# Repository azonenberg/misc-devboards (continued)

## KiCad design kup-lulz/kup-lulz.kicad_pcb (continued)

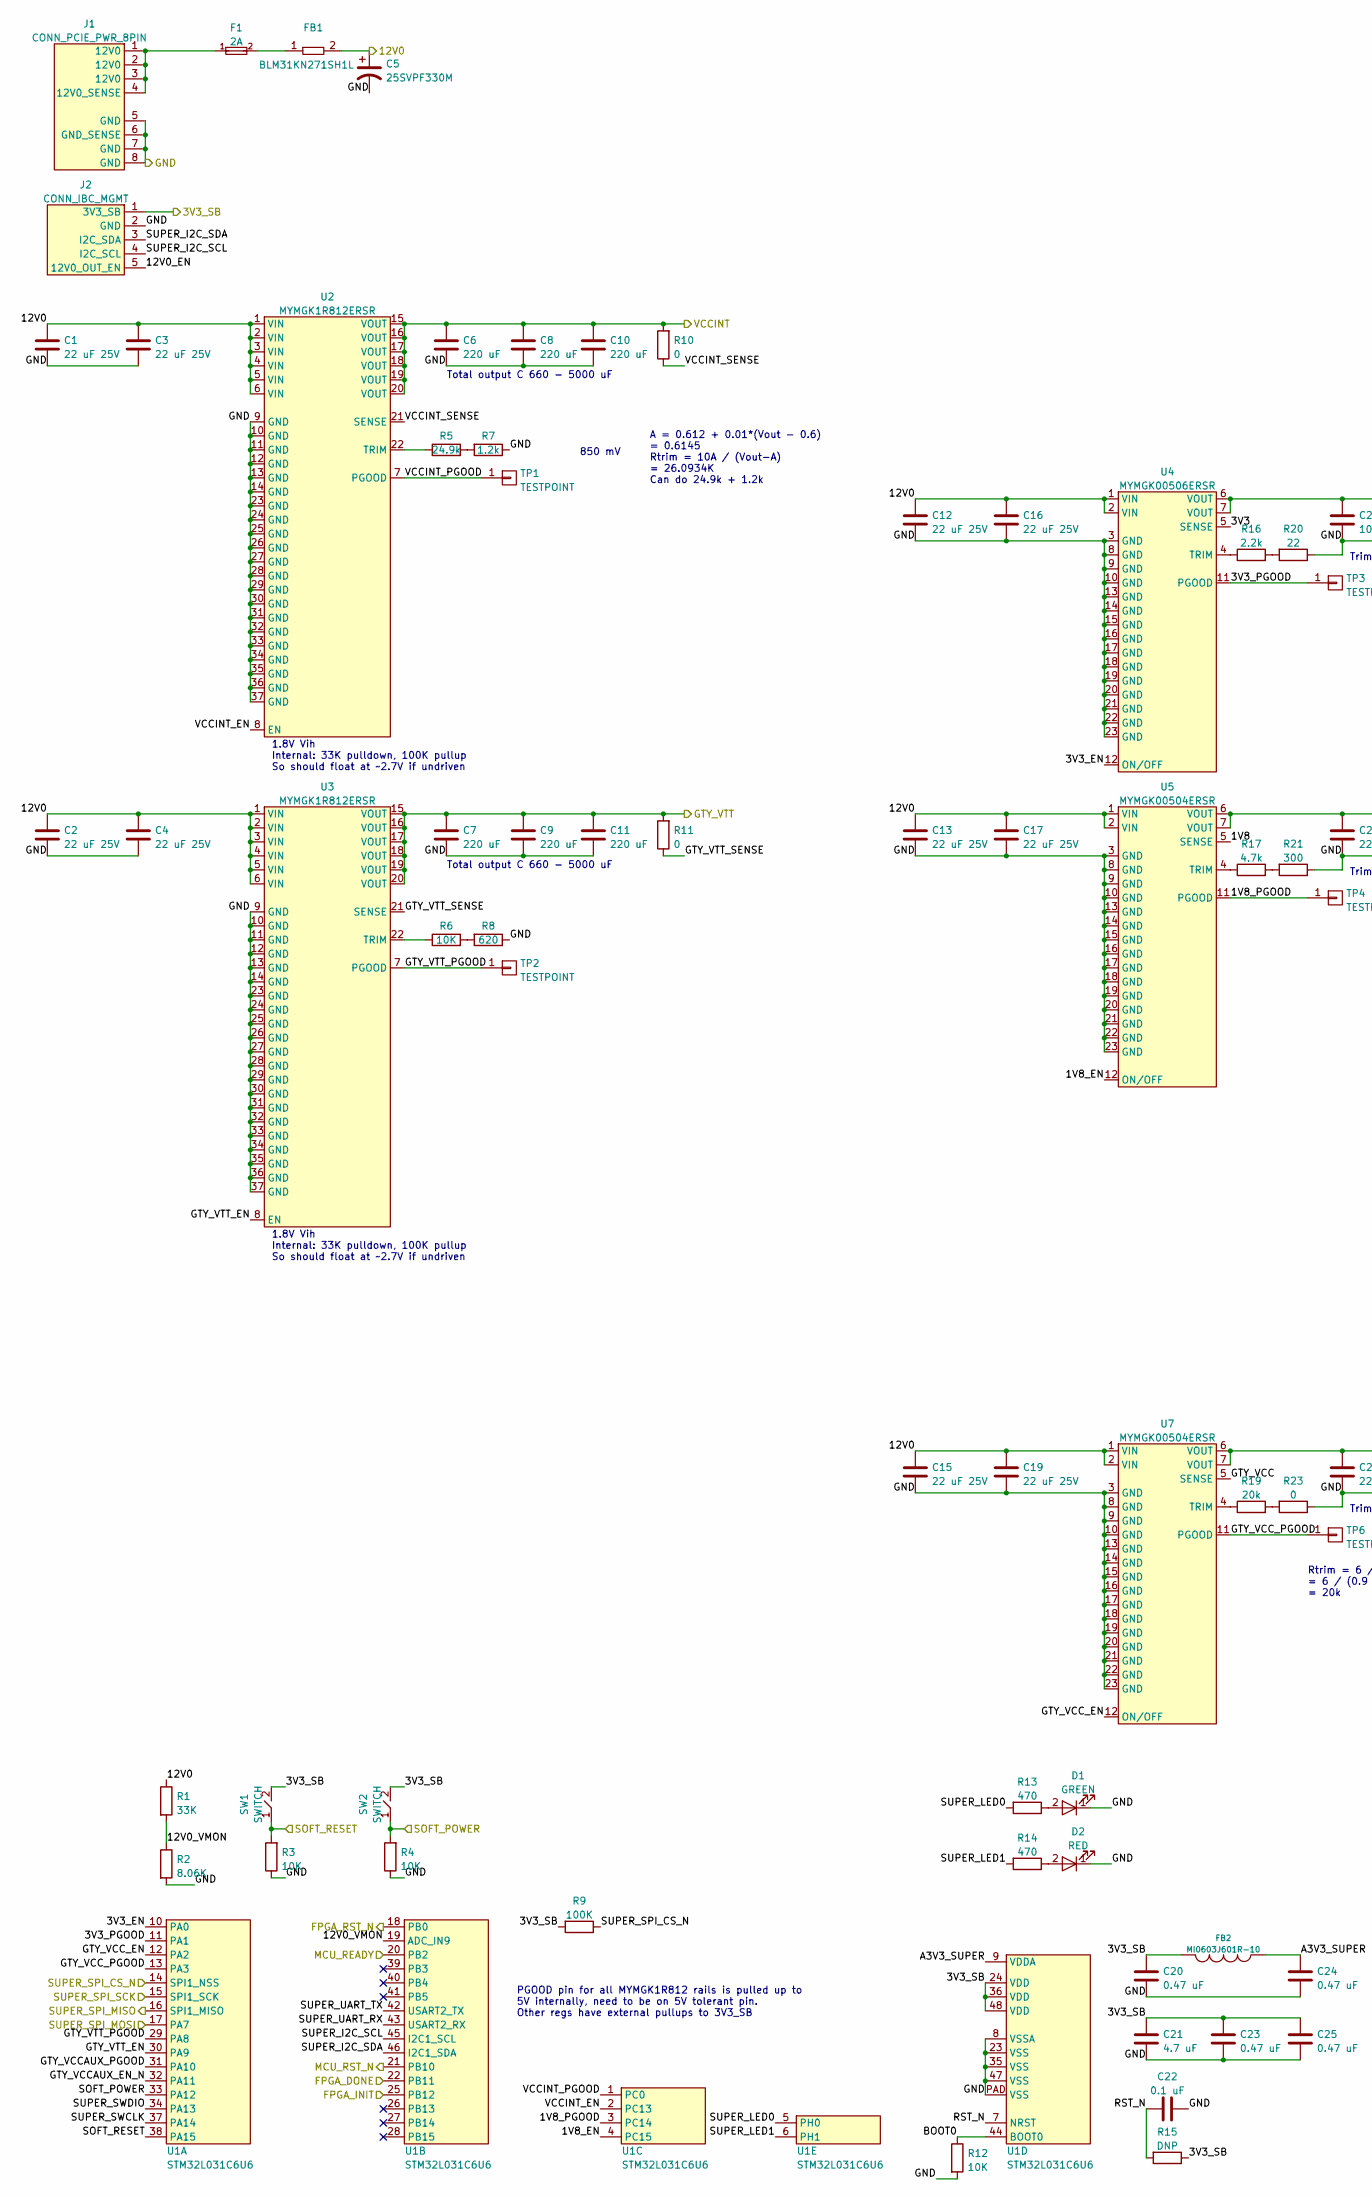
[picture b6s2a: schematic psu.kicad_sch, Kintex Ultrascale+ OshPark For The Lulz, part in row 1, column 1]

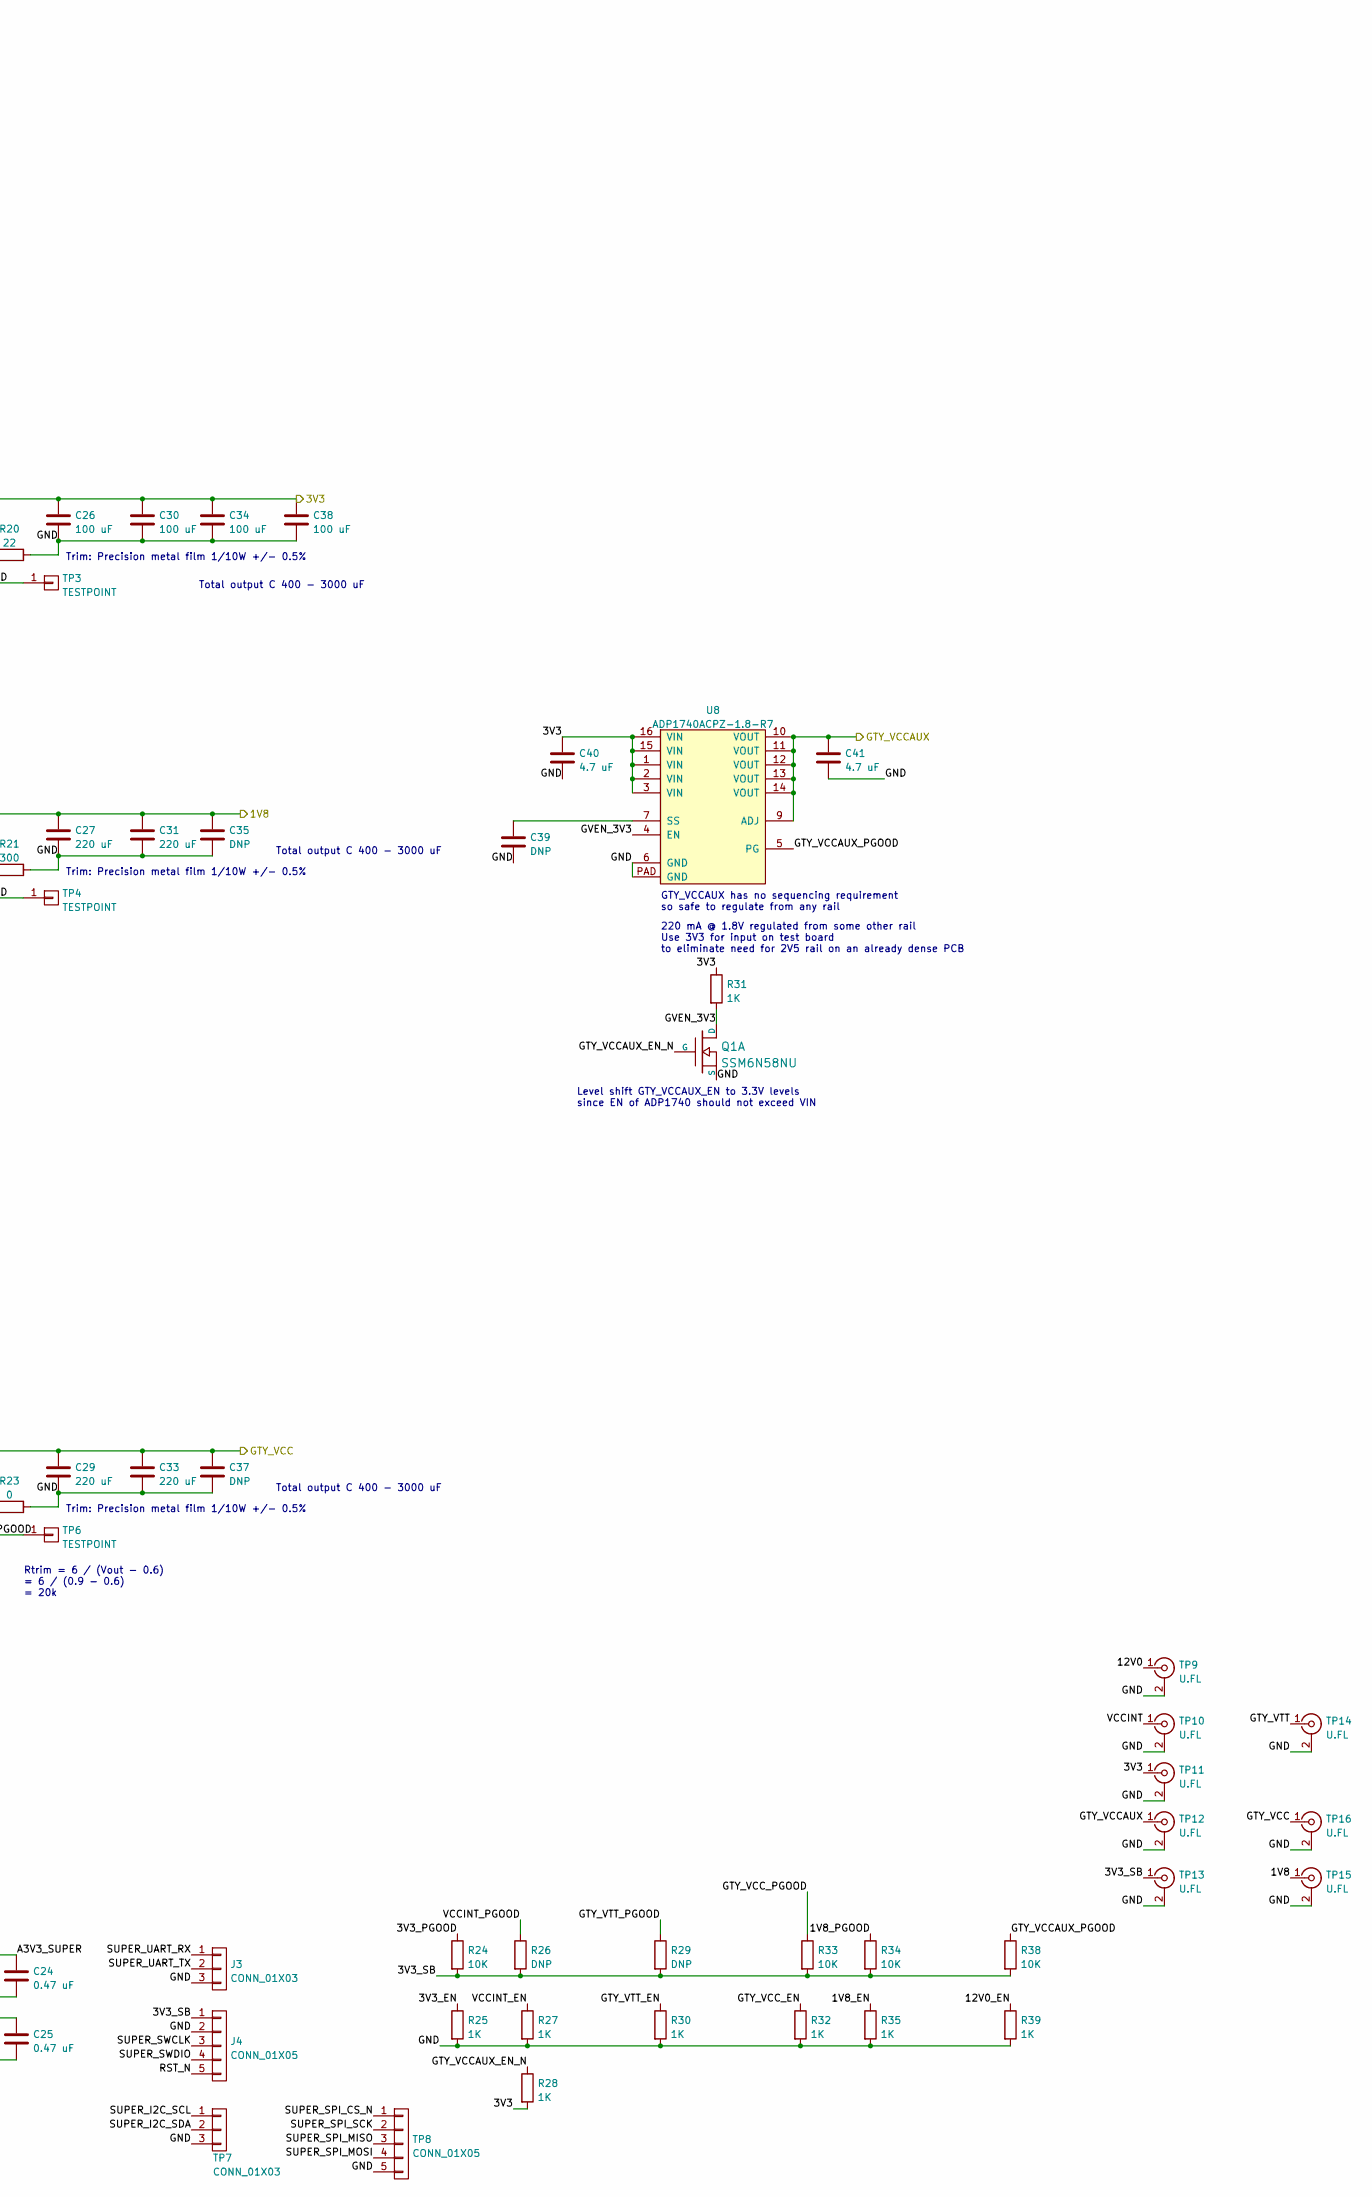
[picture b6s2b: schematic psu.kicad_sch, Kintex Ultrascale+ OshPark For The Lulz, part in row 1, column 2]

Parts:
C1, C2, C3, C4, C12, C13, C15, C16, C17, C19: 22 uF 25V; EIA_1812_CAP_NOSILK
C5: 25SVPF330M; CAP_AL_10MM_SMT
C6, C7, C8, C9, C10, C11, C27, C29, C31, C33: 220 uF; EIA_1210_CAP_NOSILK
C20, C23, C24, C25: 0.47 uF; EIA_0402_CAP_NOSILK
C21, C40, C41: 4.7 uF; EIA_0603_CAP_NOSILK
C22: 0.1 uF; EIA_0402_CAP_NOSILK
C26, C30, C34, C38: 100 uF; EIA_1210_CAP_NOSILK
C35, C37: DNP; EIA_1210_CAP_NOSILK
C39: DNP; EIA_0402_CAP_NOSILK
D1: GREEN; EIA_0603_LED
D2: RED; EIA_0603_LED
F1: 2A; EIA_0603_CAP_NOSILK
FB1: BLM31KN271SH1L; EIA_1206_CAP_NOSILK
FB2: MI0603J601R-10; EIA_0603_INDUCTOR_NOSILK
J1: CONN_PCIE_PWR_8PIN; CONN_MOLEX_MINIFITJR_8POS_0039291087
J2: CONN_IBC_MGMT; CONN_MOLEX_PICOBLADE_5POS_0532610571
J3: CONN_01X03; CONN_HEADER_2.54MM_1x3
J4: CONN_01X05; CONN_HEADER_2.54MM_1x5
Q1: SSM6N58NU; DFN_6_0.65MM_2x2MM_GDS
R1: 33K; EIA_0402_RES_NOSILK
R2: 8.06K; EIA_0402_RES_NOSILK
R3, R4, R6, R12, R24, R33, R34, R38: 10K; EIA_0402_RES_NOSILK
R5: 24.9k; EIA_0402_RES_NOSILK
R7: 1.2k; EIA_0402_RES_NOSILK
R8: 620; EIA_0402_RES_NOSILK
R9: 100K; EIA_0402_RES_NOSILK
R10, R11, R23: 0; EIA_0402_RES_NOSILK
R13, R14: 470; EIA_0402_RES_NOSILK
R15, R26, R29: DNP; EIA_0402_RES_NOSILK
R16: 2.2k; EIA_0402_RES_NOSILK
R17: 4.7k; EIA_0402_RES_NOSILK
R19: 20k; EIA_0402_RES_NOSILK
R20: 22; EIA_0402_RES_NOSILK
R21: 300; EIA_0402_RES_NOSILK
R25, R27, R28, R30, R31, R32, R35, R39: 1K; EIA_0402_RES_NOSILK
SW1, SW2: SWITCH; SWITCH_RAFI_MICON_5
TP1, TP2, TP3, TP4, TP6: TESTPOINT; TESTPOINT_SMT_0.5MM
TP7: CONN_01X03; CONN_HEADER_2.54MM_1x3
TP8: CONN_01X05; CONN_HEADER_2.54MM_1x5
TP9, TP10, TP11, TP12, TP13, TP14, TP15, TP16: U.FL; CONN_U.FL_TE_1909763-1
U1: STM32L031C6U6; QFN_48_0.5MM_7x7MM
U2, U3: MYMGK1R812ERSR; MODULE_MURATA_MYMGK1R812
U4: MYMGK00506ERSR; MODULE_MURATA_MYMGK00504ERSR
U5, U7: MYMGK00504ERSR; MODULE_MURATA_MYMGK00504ERSR
U8: ADP1740ACPZ-1.8-R7; QFN_16_0.65MM_4x4MM

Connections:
/3V3: C26.1, C30.1, C34.1, C38.1, C40.1, R28.2, R31.1, TP11.1 (In), U4.5 (SENSE), U4.6 (VOUT), U4.7 (VOUT), U8.1 (VIN), U8.2 (VIN), U8.3 (VIN), U8.15 (VIN), U8.16 (VIN); also elsewhere on the board
/3V3_SB: C20.1, C21.1, C23.1, C25.1, FB2.2, J2.1 (3V3_SB), J4.1, R9.2, R15.1, R24.2, R26.2, R29.2, R33.2, R34.2, R38.2, SW1.2, SW2.2, TP13.1 (In), U1.24 (VDD), U1.36 (VDD), U1.48 (VDD)
/12V0: C1.1, C2.1, C3.1, C4.1, C5.1, C12.1, C13.1, C15.1, C16.1, C17.1, C19.1, FB1.2, R1.1, TP9.1 (In), U2.1 (VIN), U2.2 (VIN), U2.3 (VIN), U2.4 (VIN), U2.5 (VIN), U2.6 (VIN), U3.1 (VIN), U3.2 (VIN), U3.3 (VIN), U3.4 (VIN), U3.5 (VIN), U3.6 (VIN), U4.1 (VIN), U4.2 (VIN), U5.1 (VIN), U5.2 (VIN), U7.1 (VIN), U7.2 (VIN)
/FPGA support/1V8: C27.1, C31.1, C35.1, TP15.1 (In), U5.5 (SENSE), U5.6 (VOUT), U5.7 (VOUT); also elsewhere on the board
/FPGA support/FPGA_DONE_3V3: U1.22 (PB11); also elsewhere on the board
/FPGA support/FPGA_INIT_3V3: U1.25 (PB12); also elsewhere on the board
/FPGA support/FPGA_RESET_N_3V3: U1.18 (PB0); also elsewhere on the board
/FPGA support/VCCINT: C6.1, C8.1, C10.1, R10.2, TP10.1 (In), U2.15 (VOUT), U2.16 (VOUT), U2.17 (VOUT), U2.18 (VOUT), U2.19 (VOUT), U2.20 (VOUT); also elsewhere on the board
/GND: C1.2, C2.2, C3.2, C4.2, C5.2, C6.2, C7.2, C8.2, C9.2, C10.2, C11.2, C12.2, C13.2, C15.2, C16.2, C17.2, C19.2, C20.2, C21.2, C22.2, C23.2, C24.2, C25.2, C26.2, C27.2, C29.2, C30.2, C31.2, C33.2, C34.2, C35.2, C37.2, C38.2, C39.2, C40.2, C41.2, D1.1 (K), D2.1 (K), J1.5 (GND), J1.6 (GND_SENSE), J1.7 (GND), J1.8 (GND), J2.2 (GND), J3.3, J4.2, Q1.S1 (S), R2.2, R3.1, R4.1, R7.1, R8.1, R12.2, R20.1, R21.1, R23.1, R25.2, R27.2, R30.2, R32.2, R35.2, R39.2, TP7.3, TP8.5, TP9.2 (Ext), TP10.2 (Ext), TP11.2 (Ext), TP12.2 (Ext), TP13.2 (Ext), TP14.2 (Ext), TP15.2 (Ext), TP16.2 (Ext), U1.8 (VSSA), U1.23 (VSS), U1.35 (VSS), U1.47 (VSS), U1.PAD (VSS), U2.9 (GND), U2.10 (GND), U2.11 (GND), U2.12 (GND), U2.13 (GND), U2.14 (GND), U2.23 (GND), U2.24 (GND), U2.25 (GND), U2.26 (GND), U2.27 (GND), U2.28 (GND), U2.29 (GND), U2.30 (GND), U2.31 (GND), U2.32 (GND), U2.33 (GND), U2.34 (GND), U2.35 (GND), U2.36 (GND), U2.37 (GND), U3.9 (GND), U3.10 (GND), U3.11 (GND), U3.12 (GND), U3.13 (GND), U3.14 (GND), U3.23 (GND), U3.24 (GND), U3.25 (GND), U3.26 (GND), U3.27 (GND), U3.28 (GND), U3.29 (GND), U3.30 (GND), U3.31 (GND), U3.32 (GND), U3.33 (GND), U3.34 (GND), U3.35 (GND), U3.36 (GND), U3.37 (GND), U4.3 (GND), U4.8 (GND), U4.9 (GND), U4.10 (GND), U4.13 (GND), U4.14 (GND), U4.15 (GND), U4.16 (GND), U4.17 (GND), U4.18 (GND), U4.19 (GND), U4.20 (GND), U4.21 (GND), U4.22 (GND), U4.23 (GND), U5.3 (GND), U5.8 (GND), U5.9 (GND), U5.10 (GND), U5.13 (GND), U5.14 (GND), U5.15 (GND), U5.16 (GND), U5.17 (GND), U5.18 (GND), U5.19 (GND), U5.20 (GND), U5.21 (GND), U5.22 (GND), U5.23 (GND), U7.3 (GND), U7.8 (GND), U7.9 (GND), U7.10 (GND), U7.13 (GND), U7.14 (GND), U7.15 (GND), U7.16 (GND), U7.17 (GND), U7.18 (GND), U7.19 (GND), U7.20 (GND), U7.21 (GND), U7.22 (GND), U7.23 (GND), U8.6 (GND), U8.PAD (GND); also elsewhere on the board
/GTY_VTT: C7.1, C9.1, C11.1, R11.2, TP14.1 (In), U3.15 (VOUT), U3.16 (VOUT), U3.17 (VOUT), U3.18 (VOUT), U3.19 (VOUT), U3.20 (VOUT); also elsewhere on the board
/Management/MCU_READY: U1.20 (PB2); also elsewhere on the board
/Management/MCU_RST_N: U1.21 (PB10); also elsewhere on the board
/Power Supply/1V8_EN: R35.1, U1.4 (PC15), U5.12 (ON/OFF)
/Power Supply/1V8_PGOOD: R34.1, TP4.1, U1.3 (PC14), U5.11 (PGOOD)
/Power Supply/3V3_EN: R25.1, U1.10 (PA0), U4.12 (ON/OFF)
/Power Supply/3V3_PGOOD: R24.1, TP3.1, U1.11 (PA1), U4.11 (PGOOD)
/Power Supply/12V0_EN: J2.5 (12V0_OUT_EN), R39.1
/Power Supply/12V0_VMON: R1.2, R2.1, U1.19 (ADC_IN9)
/Power Supply/A3V3_SUPER: C24.1, FB2.1, U1.9 (VDDA)
/Power Supply/BOOT0: R12.1, U1.44 (BOOT0)
/Power Supply/GTY_VCC: C29.1, C33.1, C37.1, TP16.1 (In), U7.5 (SENSE), U7.6 (VOUT), U7.7 (VOUT); also elsewhere on the board
/Power Supply/GTY_VCCAUX: C41.1, TP12.1 (In), U8.9 (ADJ), U8.10 (VOUT), U8.11 (VOUT), U8.12 (VOUT), U8.13 (VOUT), U8.14 (VOUT); also elsewhere on the board
/Power Supply/GTY_VCCAUX_EN_N: Q1.G1 (G), R28.1, U1.32 (PA11)
/Power Supply/GTY_VCCAUX_PGOOD: R38.1, U1.31 (PA10), U8.5 (PG)
/Power Supply/GTY_VCC_EN: R32.1, U1.12 (PA2), U7.12 (ON/OFF)
/Power Supply/GTY_VCC_PGOOD: R33.1, TP6.1, U1.13 (PA3), U7.11 (PGOOD)
/Power Supply/GTY_VTT_EN: R30.1, U1.30 (PA9), U3.8 (EN)
/Power Supply/GTY_VTT_PGOOD: R29.1, TP2.1, U1.29 (PA8), U3.7 (PGOOD)
/Power Supply/GTY_VTT_SENSE: R11.1, U3.21 (SENSE)
/Power Supply/GVEN_3V3: Q1.D1 (D), R31.2, U8.4 (EN)
/Power Supply/RST_N: C22.1, J4.5, R15.2, U1.7 (NRST)
/Power Supply/SOFT_POWER: R4.2, SW2.1, U1.33 (PA12); also elsewhere on the board
/Power Supply/SOFT_RESET: R3.2, SW1.1, U1.38 (PA15); also elsewhere on the board
/Power Supply/SUPER_I2C_SCL: J2.4 (I2C_SCL), TP7.1, U1.45 (I2C1_SCL)
/Power Supply/SUPER_I2C_SDA: J2.3 (I2C_SDA), TP7.2, U1.46 (I2C1_SDA)
/Power Supply/SUPER_LED0: R13.2, U1.5 (PH0)
/Power Supply/SUPER_LED1: R14.2, U1.6 (PH1)
/Power Supply/SUPER_SPI_CS_N: R9.1, TP8.1, U1.14 (SPI1_NSS); also elsewhere on the board
/Power Supply/SUPER_SPI_MISO: TP8.3, U1.16 (SPI1_MISO); also elsewhere on the board
/Power Supply/SUPER_SPI_MOSI: TP8.4, U1.17 (PA7); also elsewhere on the board
/Power Supply/SUPER_SPI_SCK: TP8.2, U1.15 (SPI1_SCK); also elsewhere on the board
/Power Supply/SUPER_SWCLK: J4.3, U1.37 (PA14)
/Power Supply/SUPER_SWDIO: J4.4, U1.34 (PA13)
/Power Supply/SUPER_UART_RX: J3.1, U1.43 (USART2_RX)
/Power Supply/SUPER_UART_TX: J3.2, U1.42 (USART2_TX)
/Power Supply/VCCINT_EN: R27.1, U1.2 (PC13), U2.8 (EN)
/Power Supply/VCCINT_PGOOD: R26.1, TP1.1, U1.1 (PC0), U2.7 (PGOOD)
/Power Supply/VCCINT_SENSE: R10.1, U2.21 (SENSE)
unnamed: C39.1, U8.7 (SS)
unnamed: D1.2 (A), R13.1
unnamed: D2.2 (A), R14.1
unnamed: F1.1, J1.1 (12V0), J1.2 (12V0), J1.3 (12V0), J1.4 (12V0_SENSE)
unnamed: F1.2, FB1.1
unnamed: R5.1, U2.22 (TRIM)
unnamed: R5.2, R7.2
unnamed: R6.1, U3.22 (TRIM)
unnamed: R6.2, R8.2
unnamed: R16.1, U4.4 (TRIM)
unnamed: R16.2, R20.2
unnamed: R17.1, U5.4 (TRIM)
unnamed: R17.2, R21.2
unnamed: R19.1, U7.4 (TRIM)
unnamed: R19.2, R23.2

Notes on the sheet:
Total output C 400 - 3000 uF
A = 0.612 + 0.01*(Vout - 0.6) = 0.6145 Rtrim = 10A / (Vout-A) = 26.0934K Can do 24.9k + 1.2k
Total output C 660 - 5000 uF
1.8V Vih Internal: 33K pulldown, 100K pullup So should float at ~2.7V if undriven
PGOOD pin for all MYMGK1R812 rails is pulled up to 5V internally, need to be on 5V tolerant pin. Other regs have external pullups to 3V3_SB
Trim: Precision metal film 1/10W +/- 0.5%
220 mA @ 1.8V regulated from some other rail Use 3V3 for input on test board to eliminate need for 2V5 rail on an already dense PCB
Rtrim = 6 / (Vout - 0.6) = 6 / (0.9 - 0.6) = 20k
Level shift GTY_VCCAUX_EN to 3.3V levels since EN of ADP1740 should not exceed VIN
850 mV
GTY_VCCAUX has no sequencing requirement so safe to regulate from any rail

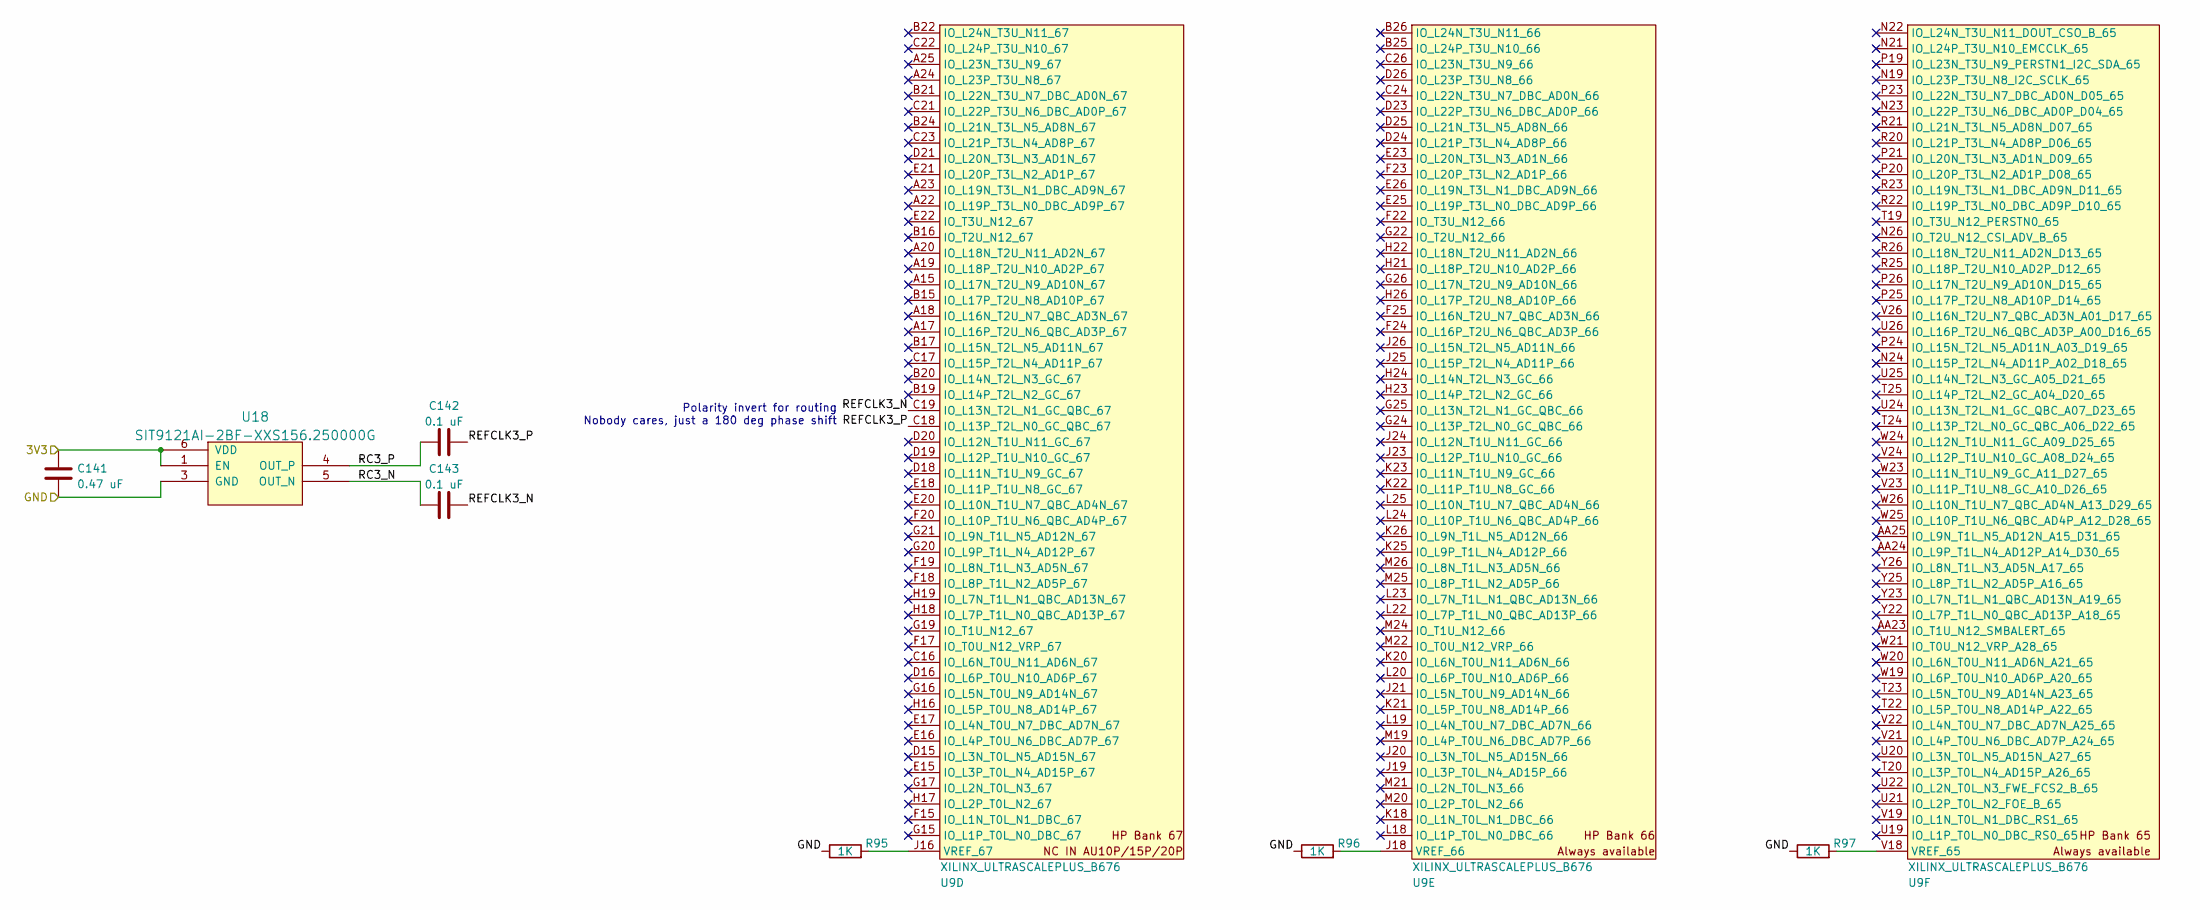
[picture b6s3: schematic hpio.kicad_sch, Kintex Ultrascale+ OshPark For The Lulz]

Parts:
C141: 0.47 uF; EIA_0402_CAP_NOSILK
C142, C143: 0.1 uF; EIA_0402_CAP_NOSILK
R95, R96, R97: 1K; EIA_0402_RES_NOSILK
U9: XILINX_ULTRASCALEPLUS_B676; BGA_676_27x27_FULLARRAY_1MM_FFG676
U18: SIT9121AI-2BF-XXS156.250000G; OSCILLATOR_LVDS_3.2x2.5

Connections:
/3V3: C141.1, U18.1 (EN), U18.6 (VDD); also elsewhere on the board
/GND: C141.2, R95.1, R96.1, R97.1, U18.3 (GND); also elsewhere on the board
/HP IOs/RC3_N: C143.1, U18.5 (OUT_N)
/HP IOs/RC3_P: C142.1, U18.4 (OUT_P)
/HP IOs/REFCLK3_N: C143.2, U9.C19 (IO_L13N_T2L_N1_GC_QBC_67)
/HP IOs/REFCLK3_P: C142.2, U9.C18 (IO_L13P_T2L_N0_GC_QBC_67)
unnamed: R95.2, U9.J16 (VREF_67)
unnamed: R96.2, U9.J18 (VREF_66)
unnamed: R97.2, U9.V18 (VREF_65)

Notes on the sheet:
Polarity invert for routing Nobody cares, just a 180 deg phase shift

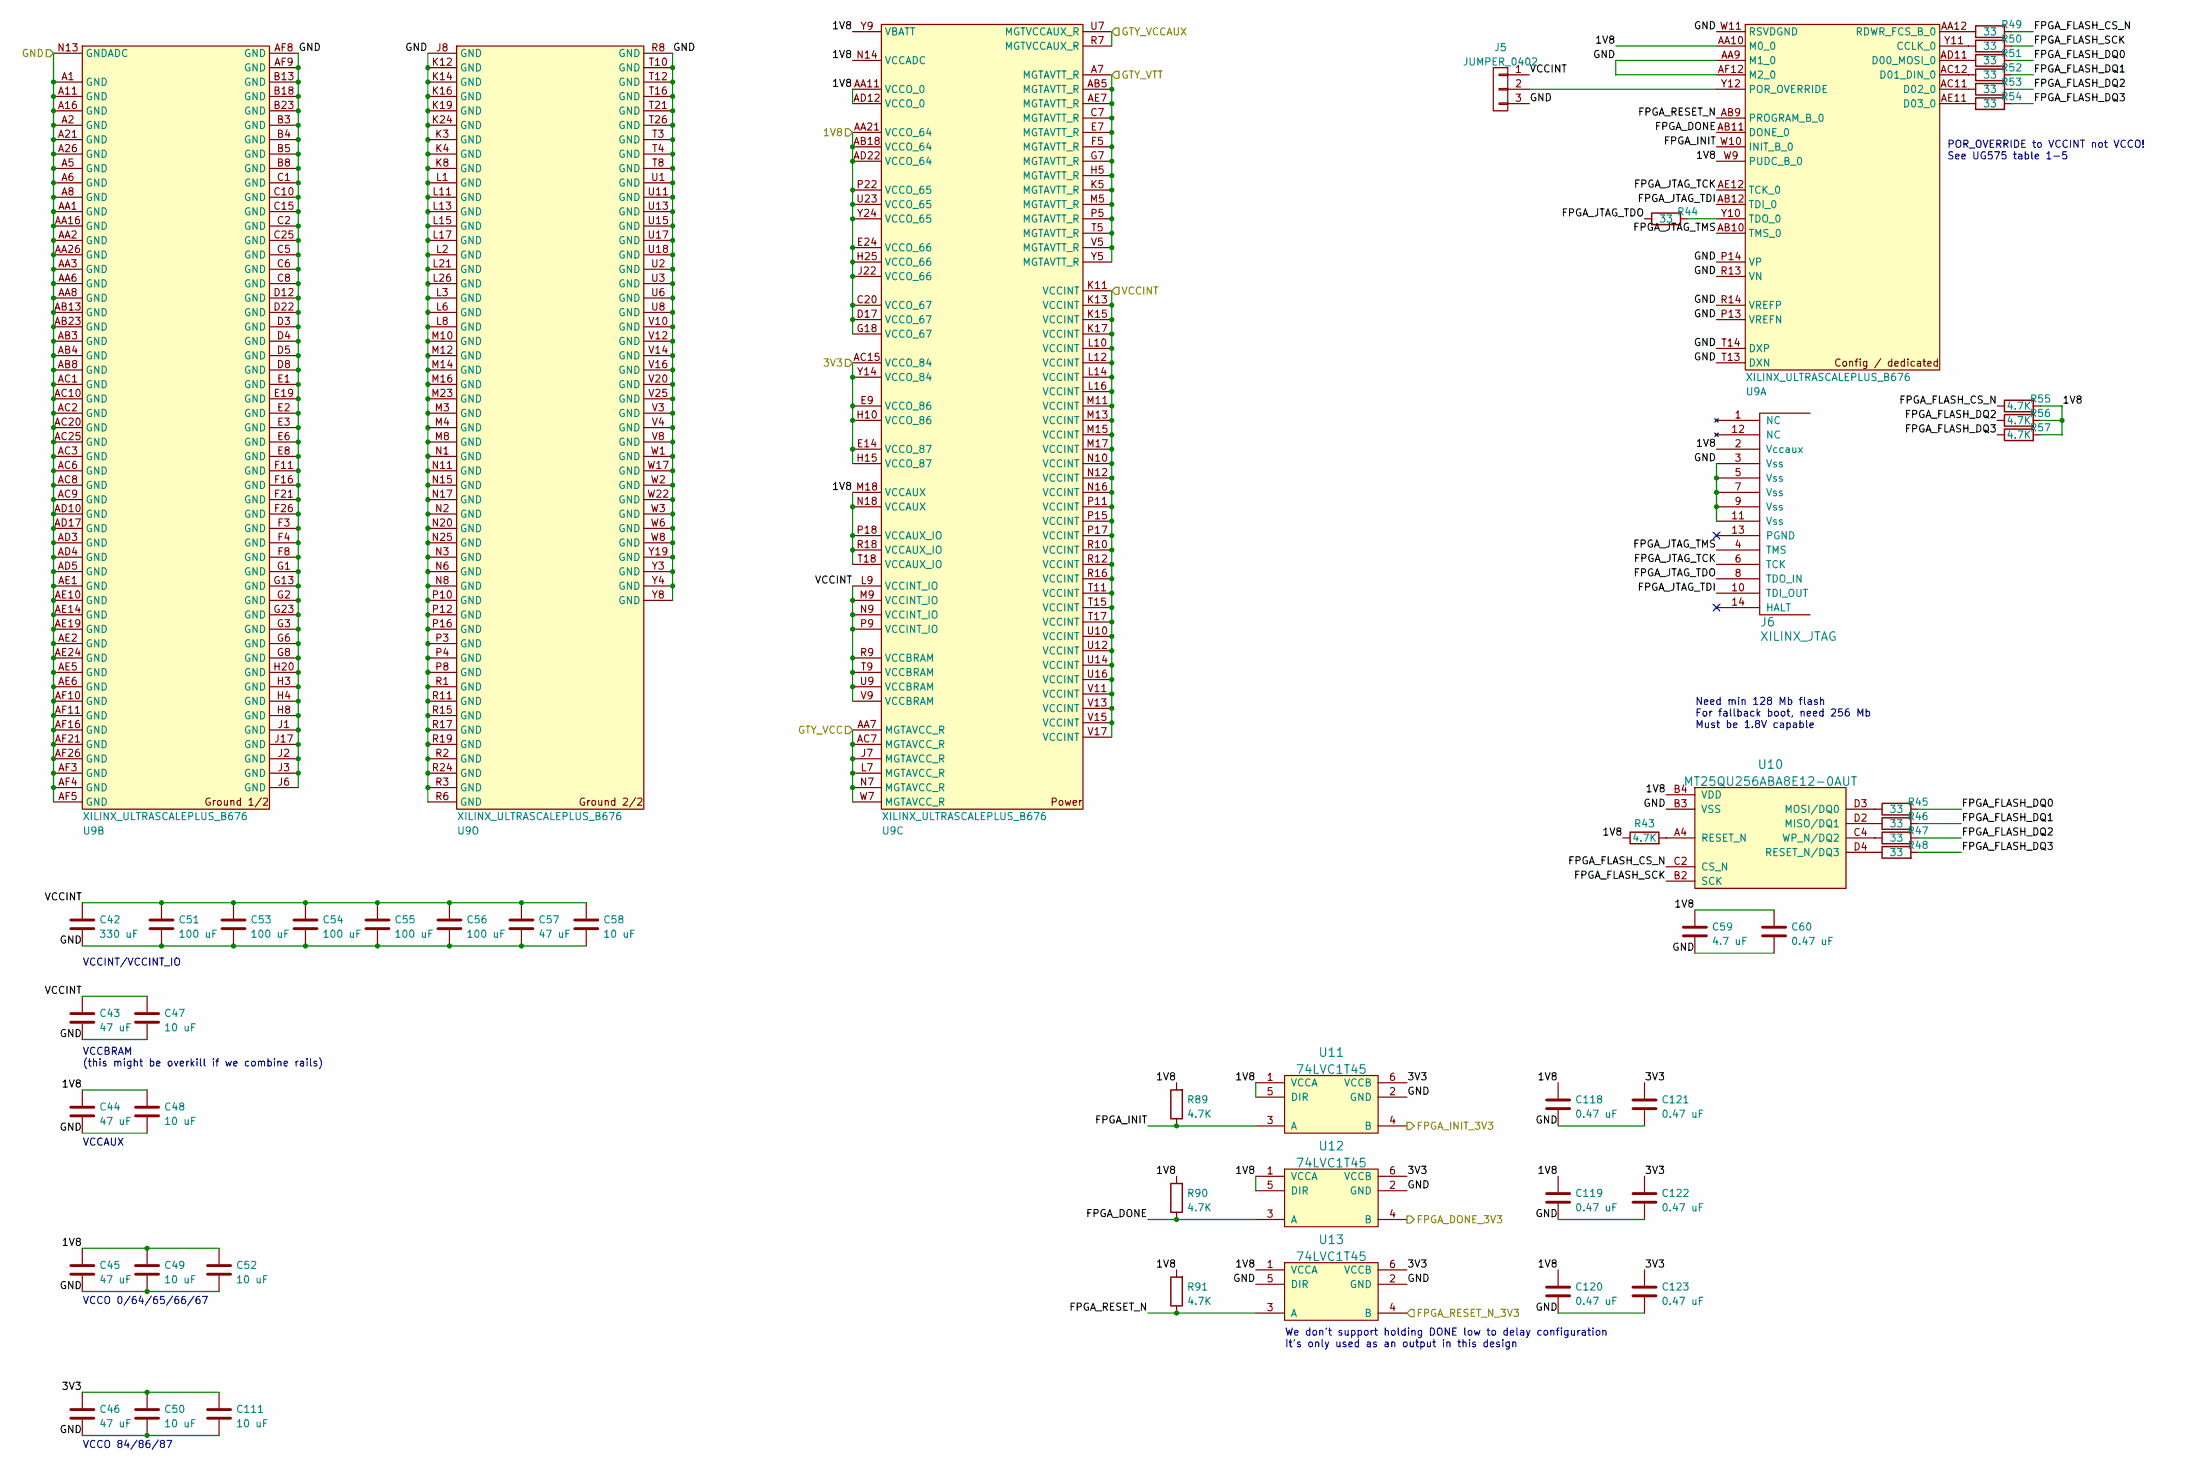
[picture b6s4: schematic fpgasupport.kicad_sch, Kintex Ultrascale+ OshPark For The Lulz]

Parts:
C42: 330 uF; EIA_1210_CAP_NOSILK
C43, C44, C45, C46, C57: 47 uF; EIA_1210_CAP_NOSILK
C47, C48, C49, C50, C52, C58, C111: 10 uF; EIA_0805_CAP_NOSILK
C51, C53, C54, C55, C56: 100 uF; EIA_1210_CAP_NOSILK
C59: 4.7 uF; EIA_0603_CAP_NOSILK
C60, C118, C119, C120, C121, C122, C123: 0.47 uF; EIA_0402_CAP_NOSILK
J5: JUMPER_0402; EIA_0402_JUMPER
J6: XILINX_JTAG; XILINX_JTAG_PTH_MOLEX_0878311420
R43, R55, R56, R57, R89, R90, R91: 4.7K; EIA_0402_RES_NOSILK
R44, R45, R46, R47, R48, R49, R50, R51, R52, R53, R54: 33; EIA_0402_RES_NOSILK
U9: XILINX_ULTRASCALEPLUS_B676; BGA_676_27x27_FULLARRAY_1MM_FFG676
U10: MT25QU256ABA8E12-0AUT; BGA_24_6x8_DEPOP1_1MM
U11, U12, U13: 74LVC1T45; DFN_6_0.5MM_1.6x1.6MM_TI_DPK

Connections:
/3V3: C46.1, C50.1, C111.1, C121.1, C122.1, C123.1, U9.AC15 (VCCO_84), U9.E9 (VCCO_86), U9.E14 (VCCO_87), U9.H10 (VCCO_86), U9.H15 (VCCO_87), U9.Y14 (VCCO_84), U11.6 (VCCB), U12.6 (VCCB), U13.6 (VCCB); also elsewhere on the board
/FPGA support/1V8: C44.1, C45.1, C48.1, C49.1, C52.1, C59.1, C60.1, C118.1, C119.1, C120.1, J6.2 (Vccaux), R43.1, R55.2, R56.2, R57.2, R89.2, R90.2, R91.2, U9.AA10 (M0_0), U9.AA11 (VCCO_0), U9.AA21 (VCCO_64), U9.AB18 (VCCO_64), U9.AD12 (VCCO_0), U9.AD22 (VCCO_64), U9.C20 (VCCO_67), U9.D17 (VCCO_67), U9.E24 (VCCO_66), U9.G18 (VCCO_67), U9.H25 (VCCO_66), U9.J22 (VCCO_66), U9.M18 (VCCAUX), U9.N14 (VCCADC), U9.N18 (VCCAUX), U9.P18 (VCCAUX_IO), U9.P22 (VCCO_65), U9.R18 (VCCAUX_IO), U9.T18 (VCCAUX_IO), U9.U23 (VCCO_65), U9.W9 (PUDC_B_0), U9.Y9 (VBATT), U9.Y24 (VCCO_65), U10.B4 (VDD), U11.1 (VCCA), U11.5 (DIR), U12.1 (VCCA), U12.5 (DIR), U13.1 (VCCA); also elsewhere on the board
/FPGA support/FPGA_DONE: R90.1, U9.AB11 (DONE_0), U12.3 (A)
/FPGA support/FPGA_DONE_3V3: U12.4 (B); also elsewhere on the board
/FPGA support/FPGA_FLASH_CS_N: R49.2, R55.1, U10.C2 (CS_N)
/FPGA support/FPGA_FLASH_DQ0: R45.2, R51.2
/FPGA support/FPGA_FLASH_DQ1: R46.2, R52.2
/FPGA support/FPGA_FLASH_DQ2: R47.2, R53.2, R56.1
/FPGA support/FPGA_FLASH_DQ3: R48.2, R54.2, R57.1
/FPGA support/FPGA_FLASH_SCK: R50.2, U10.B2 (SCK)
/FPGA support/FPGA_INIT: R89.1, U9.W10 (INIT_B_0), U11.3 (A)
/FPGA support/FPGA_INIT_3V3: U11.4 (B); also elsewhere on the board
/FPGA support/FPGA_JTAG_TCK: J6.6 (TCK), U9.AE12 (TCK_0)
/FPGA support/FPGA_JTAG_TDI: J6.10 (TDI_OUT), U9.AB12 (TDI_0)
/FPGA support/FPGA_JTAG_TDO: J6.8 (TDO_IN), R44.1
/FPGA support/FPGA_JTAG_TMS: J6.4 (TMS), U9.AB10 (TMS_0)
/FPGA support/FPGA_RESET_N: R91.1, U9.AB9 (PROGRAM_B_0), U13.3 (A)
/FPGA support/FPGA_RESET_N_3V3: U13.4 (B); also elsewhere on the board
/FPGA support/VCCINT: C42.1, C43.1, C47.1, C51.1, C53.1, C54.1, C55.1, C56.1, C57.1, C58.1, J5.1, U9.K11 (VCCINT), U9.K13 (VCCINT), U9.K15 (VCCINT), U9.K17 (VCCINT), U9.L9 (VCCINT_IO), U9.L10 (VCCINT), U9.L12 (VCCINT), U9.L14 (VCCINT), U9.L16 (VCCINT), U9.M9 (VCCINT_IO), U9.M11 (VCCINT), U9.M13 (VCCINT), U9.M15 (VCCINT), U9.M17 (VCCINT), U9.N9 (VCCINT_IO), U9.N10 (VCCINT), U9.N12 (VCCINT), U9.N16 (VCCINT), U9.P9 (VCCINT_IO), U9.P11 (VCCINT), U9.P15 (VCCINT), U9.P17 (VCCINT), U9.R9 (VCCBRAM), U9.R10 (VCCINT), U9.R12 (VCCINT), U9.R16 (VCCINT), U9.T9 (VCCBRAM), U9.T11 (VCCINT), U9.T15 (VCCINT), U9.T17 (VCCINT), U9.U9 (VCCBRAM), U9.U10 (VCCINT), U9.U12 (VCCINT), U9.U14 (VCCINT), U9.U16 (VCCINT), U9.V9 (VCCBRAM), U9.V11 (VCCINT), U9.V13 (VCCINT), U9.V15 (VCCINT), U9.V17 (VCCINT); also elsewhere on the board
/GND: C42.2, C43.2, C44.2, C45.2, C46.2, C47.2, C48.2, C49.2, C50.2, C51.2, C52.2, C53.2, C54.2, C55.2, C56.2, C57.2, C58.2, C59.2, C60.2, C111.2, C118.2, C119.2, C120.2, C121.2, C122.2, C123.2, J5.3, J6.3 (Vss), J6.5 (Vss), J6.7 (Vss), J6.9 (Vss), J6.11 (Vss), U9.A1 (GND), U9.A2 (GND), U9.A5 (GND), U9.A6 (GND), U9.A8 (GND), U9.A11 (GND), U9.A16 (GND), U9.A21 (GND), U9.A26 (GND), U9.AA1 (GND), U9.AA2 (GND), U9.AA3 (GND), U9.AA6 (GND), U9.AA8 (GND), U9.AA9 (M1_0), U9.AA16 (GND), U9.AA26 (GND), U9.AB3 (GND), U9.AB4 (GND), U9.AB8 (GND), U9.AB13 (GND), U9.AB23 (GND), U9.AC1 (GND), U9.AC2 (GND), U9.AC3 (GND), U9.AC6 (GND), U9.AC8 (GND), U9.AC9 (GND), U9.AC10 (GND), U9.AC20 (GND), U9.AC25 (GND), U9.AD3 (GND), U9.AD4 (GND), U9.AD5 (GND), U9.AD10 (GND), U9.AD17 (GND), U9.AE1 (GND), U9.AE2 (GND), U9.AE5 (GND), U9.AE6 (GND), U9.AE10 (GND), U9.AE14 (GND), U9.AE19 (GND), U9.AE24 (GND), U9.AF3 (GND), U9.AF4 (GND), U9.AF5 (GND), U9.AF8 (GND), U9.AF9 (GND), U9.AF10 (GND), U9.AF11 (GND), U9.AF12 (M2_0), U9.AF16 (GND), U9.AF21 (GND), U9.AF26 (GND), U9.B3 (GND), U9.B4 (GND), U9.B5 (GND), U9.B8 (GND), U9.B13 (GND), U9.B18 (GND), U9.B23 (GND), U9.C1 (GND), U9.C2 (GND), U9.C5 (GND), U9.C6 (GND), U9.C8 (GND), U9.C10 (GND), U9.C15 (GND), U9.C25 (GND), U9.D3 (GND), U9.D4 (GND), U9.D5 (GND), U9.D8 (GND), U9.D12 (GND), U9.D22 (GND), U9.E1 (GND), U9.E2 (GND), U9.E3 (GND), U9.E6 (GND), U9.E8 (GND), U9.E19 (GND), U9.F3 (GND), U9.F4 (GND), U9.F8 (GND), U9.F11 (GND), U9.F16 (GND), U9.F21 (GND), U9.F26 (GND), U9.G1 (GND), U9.G2 (GND), U9.G3 (GND), U9.G6 (GND), U9.G8 (GND), U9.G13 (GND), U9.G23 (GND), U9.H3 (GND), U9.H4 (GND), U9.H8 (GND), U9.H20 (GND), U9.J1 (GND), U9.J2 (GND), U9.J3 (GND), U9.J6 (GND), U9.J8 (GND), U9.J17 (GND), U9.K3 (GND), U9.K4 (GND), U9.K8 (GND), U9.K12 (GND), U9.K14 (GND), U9.K16 (GND), U9.K19 (GND), U9.K24 (GND), U9.L1 (GND), U9.L2 (GND), U9.L3 (GND), U9.L6 (GND), U9.L8 (GND), U9.L11 (GND), U9.L13 (GND), U9.L15 (GND), U9.L17 (GND), U9.L21 (GND), U9.L26 (GND), U9.M3 (GND), U9.M4 (GND), U9.M8 (GND), U9.M10 (GND), U9.M12 (GND), U9.M14 (GND), U9.M16 (GND), U9.M23 (GND), U9.N1 (GND), U9.N2 (GND), U9.N3 (GND), U9.N6 (GND), U9.N8 (GND), U9.N11 (GND), U9.N13 (GNDADC), U9.N15 (GND), U9.N17 (GND), U9.N20 (GND), U9.N25 (GND), U9.P3 (GND), U9.P4 (GND), U9.P8 (GND), U9.P10 (GND), U9.P12 (GND), U9.P13 (VREFN), U9.P14 (VP), U9.P16 (GND), U9.R1 (GND), U9.R2 (GND), U9.R3 (GND), U9.R6 (GND), U9.R8 (GND), U9.R11 (GND), U9.R13 (VN), U9.R14 (VREFP), U9.R15 (GND), U9.R17 (GND), U9.R19 (GND), U9.R24 (GND), U9.T3 (GND), U9.T4 (GND), U9.T8 (GND), U9.T10 (GND), U9.T12 (GND), U9.T13 (DXN), U9.T14 (DXP), U9.T16 (GND), U9.T21 (GND), U9.T26 (GND), U9.U1 (GND), U9.U2 (GND), U9.U3 (GND), U9.U6 (GND), U9.U8 (GND), U9.U11 (GND), U9.U13 (GND), U9.U15 (GND), U9.U17 (GND), U9.U18 (GND), U9.V3 (GND), U9.V4 (GND), U9.V8 (GND), U9.V10 (GND), U9.V12 (GND), U9.V14 (GND), U9.V16 (GND), U9.V20 (GND), U9.V25 (GND), U9.W1 (GND), U9.W2 (GND), U9.W3 (GND), U9.W6 (GND), U9.W8 (GND), U9.W11 (RSVDGND), U9.W17 (GND), U9.W22 (GND), U9.Y3 (GND), U9.Y4 (GND), U9.Y8 (GND), U9.Y19 (GND), U10.B3 (VSS), U11.2 (GND), U12.2 (GND), U13.2 (GND), U13.5 (DIR); also elsewhere on the board
/GTY_VTT: U9.A7 (MGTAVTT_R), U9.AB5 (MGTAVTT_R), U9.AE7 (MGTAVTT_R), U9.C7 (MGTAVTT_R), U9.E7 (MGTAVTT_R), U9.F5 (MGTAVTT_R), U9.G7 (MGTAVTT_R), U9.H5 (MGTAVTT_R), U9.K5 (MGTAVTT_R), U9.M5 (MGTAVTT_R), U9.P5 (MGTAVTT_R), U9.T5 (MGTAVTT_R), U9.V5 (MGTAVTT_R), U9.Y5 (MGTAVTT_R); also elsewhere on the board
/Power Supply/GTY_VCC: U9.AA7 (MGTAVCC_R), U9.AC7 (MGTAVCC_R), U9.J7 (MGTAVCC_R), U9.L7 (MGTAVCC_R), U9.N7 (MGTAVCC_R), U9.W7 (MGTAVCC_R); also elsewhere on the board
/Power Supply/GTY_VCCAUX: U9.R7 (MGTVCCAUX_R), U9.U7 (MGTVCCAUX_R); also elsewhere on the board
unnamed: J5.2, U9.Y12 (POR_OVERRIDE)
unnamed: R43.2, U10.A4 (RESET_N)
unnamed: R44.2, U9.Y10 (TDO_0)
unnamed: R45.1, U10.D3 (MOSI/DQ0)
unnamed: R46.1, U10.D2 (MISO/DQ1)
unnamed: R47.1, U10.C4 (WP_N/DQ2)
unnamed: R48.1, U10.D4 (RESET_N/DQ3)
unnamed: R49.1, U9.AA12 (RDWR_FCS_B_0)
unnamed: R50.1, U9.Y11 (CCLK_0)
unnamed: R51.1, U9.AD11 (D00_MOSI_0)
unnamed: R52.1, U9.AC12 (D01_DIN_0)
unnamed: R53.1, U9.AC11 (D02_0)
unnamed: R54.1, U9.AE11 (D03_0)

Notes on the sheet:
POR_OVERRIDE to VCCINT not VCCO! See UG575 table 1-5
VCCINT/VCCINT_IO
VCCAUX
VCCO 84/86/87
Need min 128 Mb flash For fallback boot, need 256 Mb Must be 1.8V capable
VCCBRAM (this might be overkill if we combine rails)
VCCO 0/64/65/66/67
We don't support holding DONE low to delay configuration It's only used as an output in this design
